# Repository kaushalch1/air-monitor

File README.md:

# Portable Air Quality Monitor

## Overview

this is a portable air quality monitoring device designed to measure particulate matter and environmental conditions in real time. it uses an ESP32 S3 microcontroller to collect sensor data,and display measurements, and store readings locally for later analysis.

The device supports offline data logging to a microsd card, allowing users to monitor air quality without requiring a continuous phone or internet connection.

## Features

- measures particulate matter, including pm1.0, pm2.5, and pm10, using a compatible particulate matter sensor.
- measures temperature and relative humidity using the SHT31 sensor.
- measures atmospheric pressure using the BMP280 sensor.
- displays the data by live sensor readings on an SSD1306 OLED display.
- records measurements to a microSD card in CSV format.
- uses a DS3231 real time clock for timestamps during offline logging.
- Supports Bluetooth Low Energy for wireless data monitoring.
- includes wi-fi capability for future wireless features.
  
## Hardware Components

| Name | Purpose | Quantity | Total Cost (USD) | Link | Distributor |
|---|---|---:|---:|---|---|
| DS3231M+TRL (SOIC-16W) | Real-time clock | 1 | 8.25 | [Link](https://www.lcsc.com/product-detail/C37663.html) | LCSC |
| BMP280 | Pressure sensor | 1 | 6.03 | [Link](https://www.lcsc.com/product-detail/C83291.html) | LCSC |
| ESP32-S3-WROOM-1-N16R8 | Main MCU (Wi-Fi/BLE) | 1 | 5.54 | [Link](https://www.lcsc.com/product-detail/C2913202.html) | LCSC |
| SHT31-DIS-B2.5kS | Temperature/humidity sensor | 1 | 3.41 | [Link](https://www.lcsc.com/product-detail/C80862.html) | LCSC |
| 0.91 inch OLED (ER-OLEDM0.91-1W-I2C) | Display | 1 | 2.80 | [Link](https://www.buydisplay.com/i2c-white-0-91-inch-oled-display-module-128x32-arduino-raspberry-pi) | BuyDisplay |
| BQ24074RGTR | Li-ion battery charger / power path | 1 | 1.59 | [Link](https://www.lcsc.com/product-detail/C54313.html) | LCSC |
| microSD socket (DM3AT-SF-PEJM5) | Data logging storage | 1 | 1.12 | [Link](https://www.lcsc.com/product-detail/C114218.html) | LCSC |
| USB-C receptacle (TYPE-C-31-M-12) | USB-C charging and data port | 1 | 0.19 | [Link](https://www.lcsc.com/product-detail/C165948.html) | LCSC |
| CR2032 holder (CR2032-BS-6-1) | RTC backup battery holder | 1 | 0.15 | [Link](https://www.lcsc.com/product-detail/C70377.html) | LCSC |
| AP2112K-3.3TRG1 | 3.3V LDO regulator | 1 | 0.13 | [Link](https://www.lcsc.com/product-detail/C51118.html) | LCSC |
| USBLC6-2SC6 | USB ESD protection | 1 | 0.13 | [Link](https://www.lcsc.com/product-detail/C7519.html) | LCSC |
| 4.7uH inductor 6.3x6.3mm (proxy: Chilisin MHCI06030-4R7M-R8) | Boost converter inductor | 1 | 0.11 | [Link](https://www.lcsc.com/product-detail/C108295.html) | LCSC |
| MT3608 | Boost converter | 1 | 0.08 | [Link](https://www.lcsc.com/product-detail/C84817.html) | LCSC |
| SS34 Schottky diode (SMA) | Power path / reverse protection diode | 1 | 0.07 | [Link](https://www.lcsc.com/product-detail/C2759883.html) | LCSC |
| Tact switch 6mm THT | User buttons | 3 | 0.10 | [Link](https://www.lcsc.com/search?q=tactile+switch+6x6+THT) | LCSC |
| 1x8 female socket header 2.54mm | Sensor/expansion header | 1 | 0.08 | [Link](https://www.lcsc.com/search?q=1x8+female+header+2.54mm) | LCSC |
| 10uF capacitor 0805 | Bulk/decoupling capacitors | 4 | 0.19 | [Link](https://www.lcsc.com/product-detail/C15850.html) | LCSC |
| Resistors 0805 (5.1k, 890, 1.5k, 10k, 100k, 75k) | Pull-ups, dividers, config resistors | 11 | 0.05 | [Link](https://www.lcsc.com/search?q=0805+1%25+resistor) | LCSC |
| 1uF capacitor 0805 | Filter capacitors | 3 | 0.04 | [Link](https://www.lcsc.com/search?q=CL21B105KBFNNNE) | LCSC |
| 4.7uF capacitor 0805 | Filter capacitor | 1 | 0.03 | [Link](https://www.lcsc.com/search?q=CL21A475KAQNNNE) | LCSC |
| 100nF capacitor 0805 | IC bypass capacitors | 4 | 0.03 | [Link](https://www.lcsc.com/product-detail/C1711.html) | LCSC |
| 1x2 pin header 2.54mm | Power/battery header | 1 | 0.02 | [Link](https://www.lcsc.com/search?q=1x2+pin+header+2.54mm) | LCSC |
| PCB (bare board) | Main PCB | 1 | 0.40 | [Link](https://jlcpcb.com/) | JLCPCB |
| PCB assembly (PCBA fees) | SMT + through-hole assembly fees | 1 | 8.17 | [Link](https://jlcpcb.com/) | JLCPCB |
## Software and Tools

- kica - Schematic capture and PCB design
- platformIO - Firmware development and building
- arduino framework for ESP32
- wokwi - Partial hardware simulation

## Data Logging

AirTrace records measurements locally so that monitoring can continue without a phone or internet connection.

The CSV log is intended to contain fields such as:

- Timestamp
- PM1.0 concentration
- PM2.5 concentration
- PM10 concentration
- Temperature
- Relative humidity
- Atmospheric pressure
- Battery voltage

## Hardware Assembly

1. Assemble the power supply, USB-C charging circuit, and battery connections.
2. Connect the ESP32-S3 and verify the regulated supply voltages.
3. Connect the environmental sensors to the I2C bus.
4. Connect the particulate matter sensor using its verified interface and pinout.
5. Connect the OLED display, microSD module, RTC, and buttons.
6. Check polarity, continuity, power rails, and signal connections before powering the complete circuit.
7. Test each peripheral individually before running the complete firmware.

# schematic

# pcb img:

# 3d view:

# 3d model:

# assembly model:

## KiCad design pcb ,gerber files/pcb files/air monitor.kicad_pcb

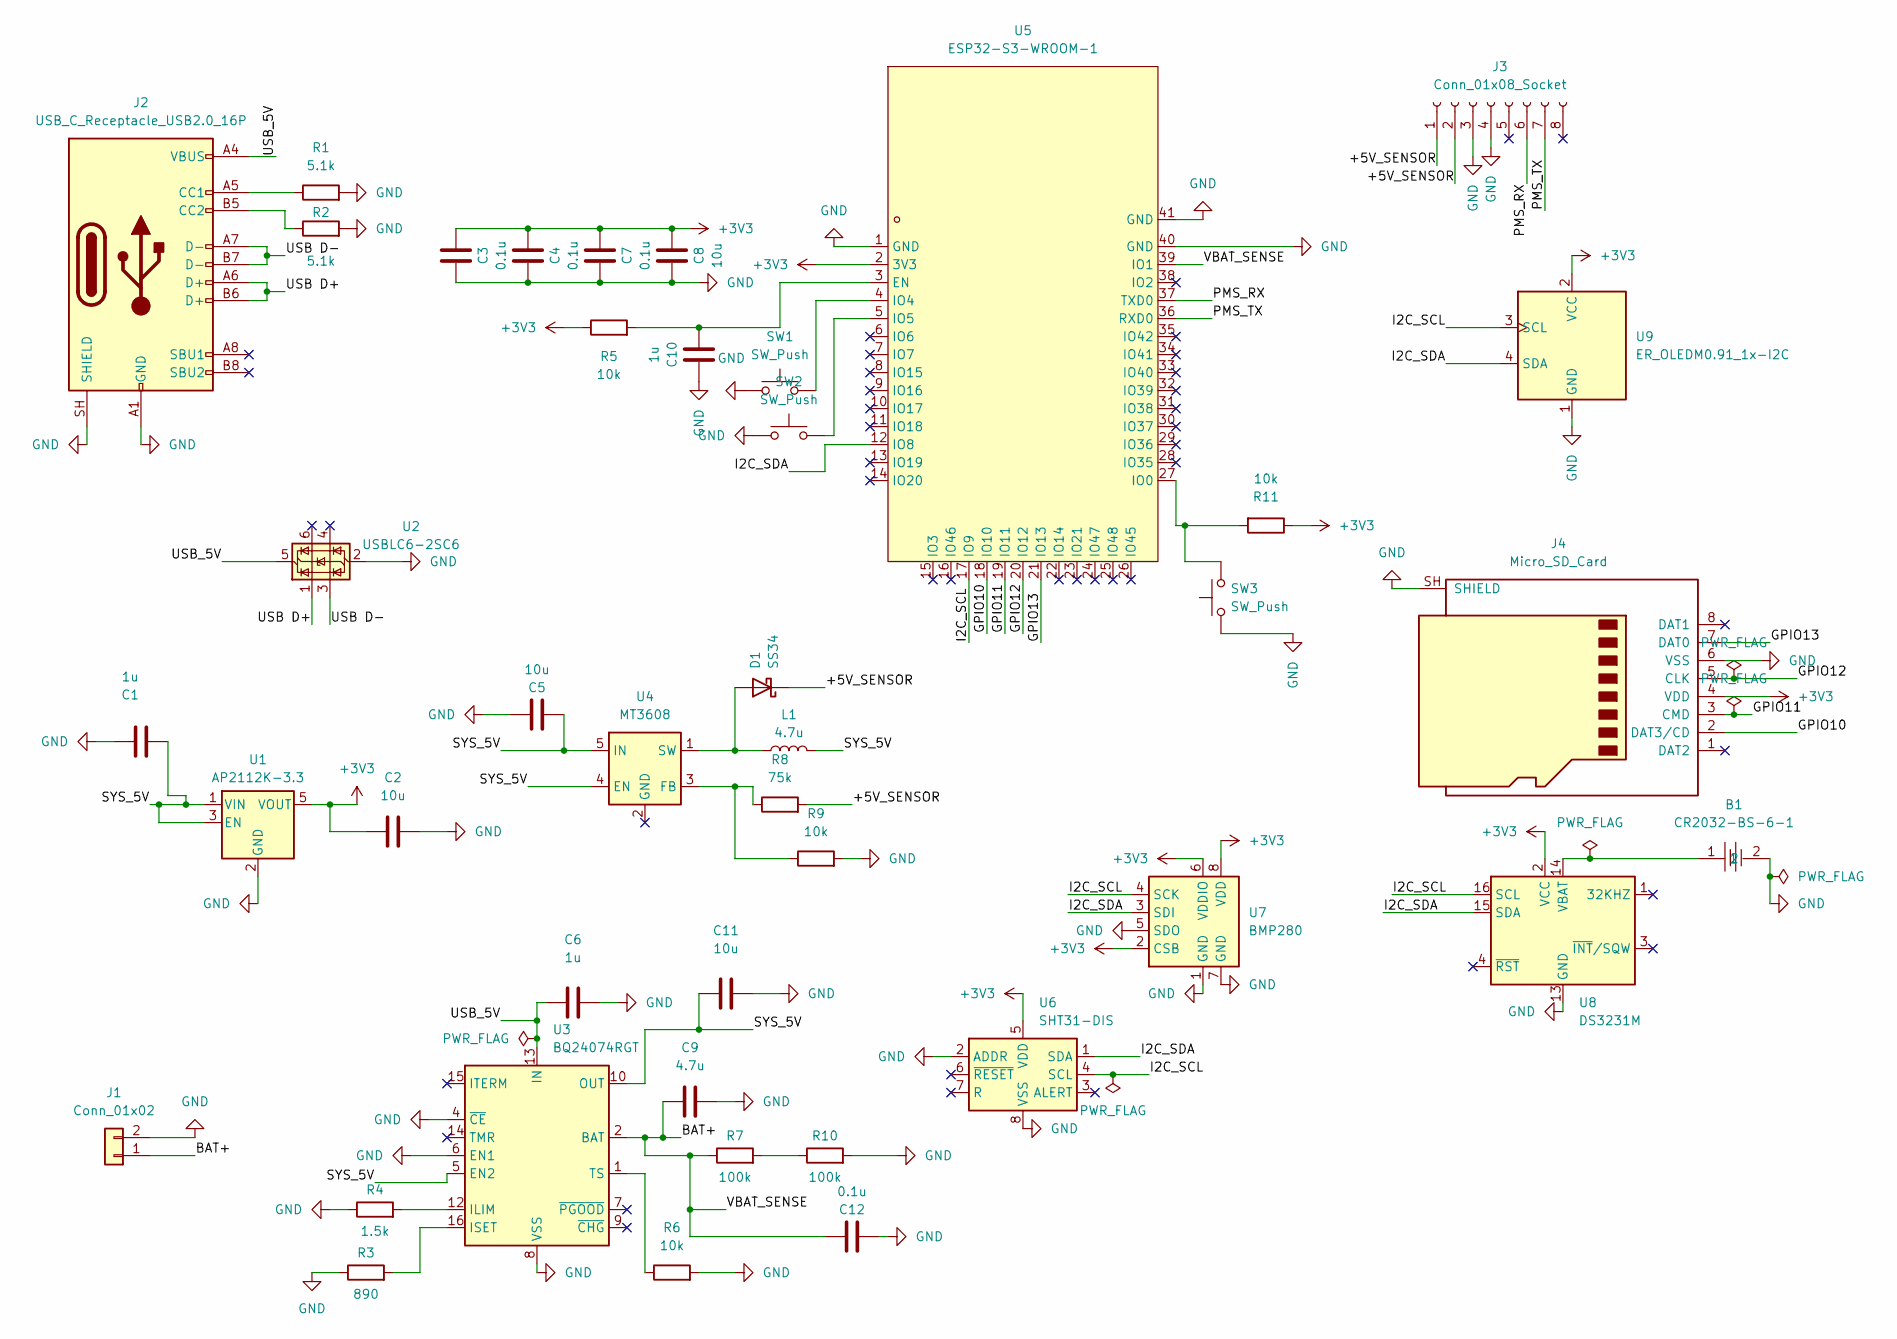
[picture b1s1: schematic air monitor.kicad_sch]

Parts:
B1: CR2032-BS-6-1; BAT-TH_CR2032-BS-6-1; MPN CR2032-BS-6-1; LCSC Part C70377
C1, C6, C10: 1u; C_0805_2012Metric
C2, C5, C8, C11: 10u; C_0805_2012Metric
C3, C4, C7, C12: 0.1u; C_0805_2012Metric
C9: 4.7u; C_0805_2012Metric
D1: SS34; D_SMA
J1: Conn_01x02; PinHeader_1x02_P2.54mm_Vertical
J2: USB_C_Receptacle_USB2.0_16P; USB_C_Receptacle_HRO_TYPE-C-31-M-12
J3: Conn_01x08_Socket; PinHeader_1x08_P2.54mm_Vertical
J4: Micro_SD_Card; microSD_HC_Hirose_DM3AT-SF-PEJM5
L1: 4.7u; L_6.3x6.3_H3
R1, R2: 5.1k; R_0805_2012Metric
R3: 890; R_0805_2012Metric
R4: 1.5k; R_0805_2012Metric
R5, R6, R9, R11: 10k; R_0805_2012Metric
R7, R10: 100k; R_0805_2012Metric
R8: 75k; R_0805_2012Metric
SW1, SW2, SW3: SW_Push; SW_PUSH_6mm
U1: AP2112K-3.3; SOT-23-5
U2: USBLC6-2SC6; SOT-23-6
U3: BQ24074RGT; VQFN-16-1EP_3x3mm_P0.5mm_EP1.6x1.6mm
U4: MT3608; SOT-23-6
U5: ESP32-S3-WROOM-1; WIRELM-SMD_ESP32-S3-WROOM-1; MPN ESP32-S3-WROOM-1-N16R8; LCSC Part C2913202
U6: SHT31-DIS; Sensirion_DFN-8-1EP_2.5x2.5mm_P0.5mm_EP1.1x1.7mm
U7: BMP280; Bosch_LGA-8_2x2.5mm_P0.65mm_ClockwisePinNumbering
U8: DS3231M; SOIC-16W_7.5x10.3mm_P1.27mm
U9: ER_OLEDM0.91_1x-I2C

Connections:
+3V3: C2.1, C3.2, C4.2, C7.2, C8.2, J4.4 (VDD), R5.1, R11.1, U1.5 (VOUT), U5.2 (3V3), U6.5 (VDD), U7.2 (CSB), U7.6 (VDDIO), U7.8 (VDD), U8.2 (VCC), U9.2 (VCC)
/+5V_SENSOR: D1.1 (K), J3.1, J3.2, R8.2
/BAT+: C9.1, C12.2, J1.1, R7.1, U3.2 (BAT), U3.3 (BAT), U5.39 (IO1)
/GPIO10: J4.2 (DAT3/CD), U5.18 (IO10)
/GPIO11: J4.3 (CMD), U5.19 (IO11)
/GPIO12: J4.5 (CLK), U5.20 (IO12)
/GPIO13: J4.7 (DAT0), U5.21 (IO13)
/I2C_SCL: U5.17 (IO9), U6.4 (SCL), U7.4 (SCK), U8.16 (SCL), U9.3 (SCL)
/I2C_SDA: U5.12 (IO8), U6.1 (SDA), U7.3 (SDI), U8.15 (SDA), U9.4 (SDA)
/PMS_RX: J3.6, U5.37 (TXD0)
/PMS_TX: J3.7, U5.36 (RXD0)
/SYS_5V: C1.1, C5.1, C11.1, L1.2, U1.1 (VIN), U1.3 (EN), U3.5 (EN2), U3.10 (OUT), U3.11 (OUT), U4.4 (EN), U4.5 (IN)
/USB D+: J2.A6 (D+), J2.B6 (D+), U2.1 (I/O1)
/USB D-: J2.A7 (D-), J2.B7 (D-), U2.3 (I/O2)
/USB_5V: C6.1, J2.A4 (VBUS), J2.A9 (VBUS), J2.B4 (VBUS), J2.B9 (VBUS), U2.5 (VBUS), U3.13 (IN)
GND: B1.2, C1.2, C2.2, C3.1, C4.1, C5.2, C6.2, C7.1, C8.1, C9.2, C10.2, C11.2, C12.1, J1.2, J2.A1 (GND), J2.A12 (GND), J2.B1 (GND), J2.B12 (GND), J2.SH (SHIELD), J3.3, J3.4, J4.6 (VSS), J4.SH (SHIELD), R1.2, R2.2, R3.1, R4.1, R6.2, R9.2, R10.2, SW1.1, SW2.1, SW3.1, U1.2 (GND), U2.2 (GND), U3.4 (~CE), U3.6 (EN1), U3.8 (VSS), U3.17 (VSS), U5.1 (GND), U5.40 (GND), U5.41 (GND), U6.2 (ADDR), U6.8 (VSS), U6.9 (VSS), U7.1 (GND), U7.5 (SDO), U7.7 (GND), U8.5 (GND), U8.6 (GND), U8.7 (GND), U8.8 (GND), U8.9 (GND), U8.10 (GND), U8.11 (GND), U8.12 (GND), U8.13 (GND), U9.1 (GND)
unnamed: D1.2 (A), L1.1, U4.1 (SW)
unnamed: J2.A5 (CC1), R1.1
unnamed: J2.B5 (CC2), R2.1
unnamed: R7.2, R10.1
unnamed: R4.2, U3.12 (ILIM)
unnamed: R3.2, U3.16 (ISET)
unnamed: R6.1, U3.1 (TS)
unnamed: R8.1, R9.1, U4.3 (FB)
unnamed: C10.1, R5.2, U5.3 (EN)
unnamed: R11.2, SW3.2, U5.27 (IO0)
unnamed: SW1.2, U5.4 (IO4)
unnamed: SW2.2, U5.5 (IO5)
unnamed: B1.1, U8.14 (VBAT)

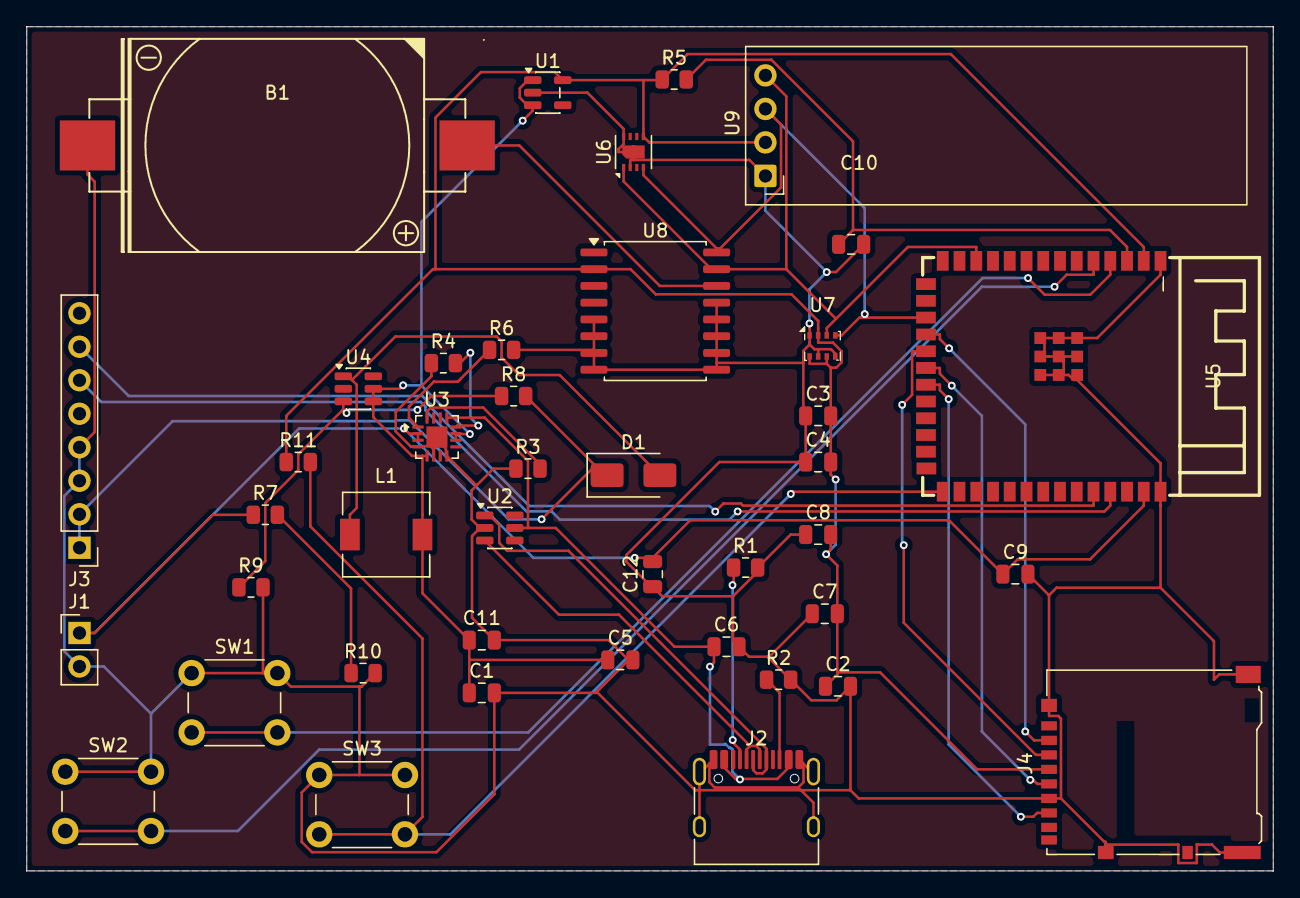
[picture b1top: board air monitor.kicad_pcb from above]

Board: 2 copper layers, 94.5 x 64.0 mm, 42 parts (0 on the bottom side), 29 nets.
